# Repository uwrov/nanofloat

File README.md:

# NanoFloat

# Helpful Links:
>[Micropython Docs](https://docs.micropython.org/en/latest/esp32/quickref.html)

>[WebREPL GitHub](https://github.com/micropython/webrepl)

>[Seeed Studio ESP32C6 (Latest Version) Pinout](https://wiki.seeedstudio.com/xiao_esp32c6_getting_started/)

>[Seeed Studio ESP32C3 Pinout](https://wiki.seeedstudio.com/xiao_esp32c6_getting_started/)

>[DRV-8833 Motor Driver Pinout and User Guide](https://lastminuteengineers.com/drv8833-arduino-tutorial/)

>[Blue Robotics Pressure Sensor](https://bluerobotics.com/store/sensors-cameras/sensors/bar02-sensor-r1-rp/)

>[Flashing Micropython Firmware Reference Guide](https://docs.micropython.org/en/latest/esp32/tutorial/intro.html#esp32-intro)

>[MS583730BA01-50 Pressure Sensor Datasheet](https://www.te.com/usa-en/product-MS583730BA01-50.datasheet.pdf)

>[MS5837 Official Python Library](https://github.com/bluerobotics/ms5837-python)

>[Standalone Pressure Sensor DigiKey Page](https://www.digikey.com/en/products/detail/te-connectivity-measurement-specialties/MS583730BA01-50/5629501)

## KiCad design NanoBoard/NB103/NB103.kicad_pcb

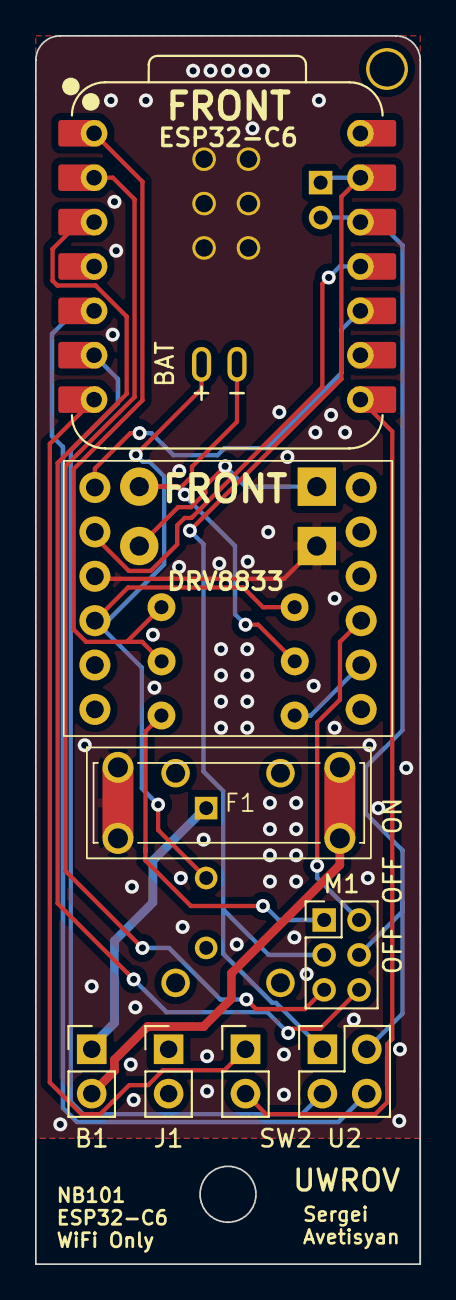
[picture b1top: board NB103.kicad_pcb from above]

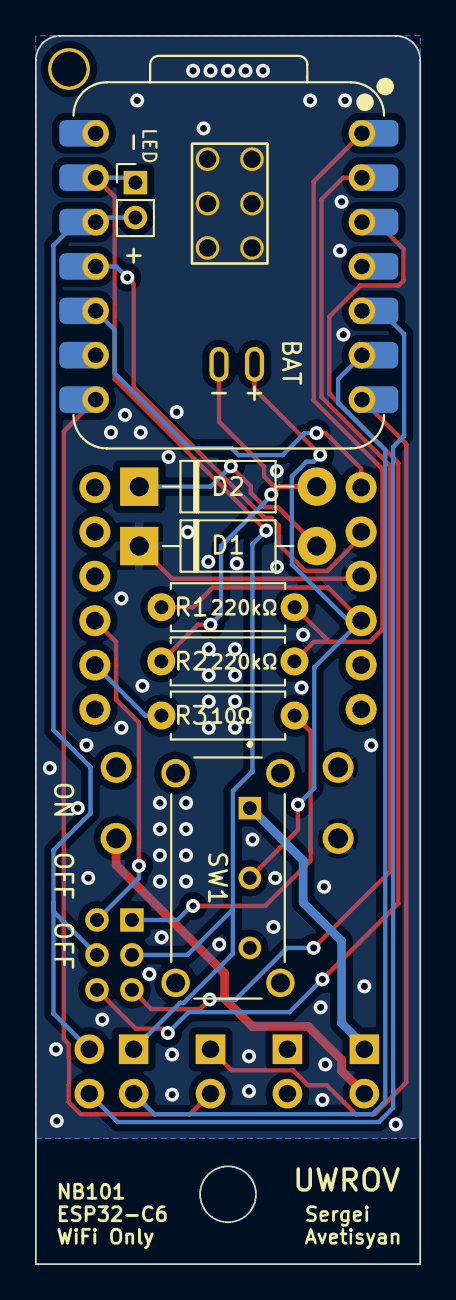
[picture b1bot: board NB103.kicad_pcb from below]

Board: 2 copper layers, 22.0 x 70.3 mm, 17 parts (8 on the bottom side), 18 nets.

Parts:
B1: 6V; PinHeader_1x02_P2.54mm_Vertical
BAT: PinHeader_1x02_P2.54mm_Vertical
D1, D2: Rectifier Diode; D_DO-41_SOD81_P10.16mm_Horizontal
F1: 0.5A Fuse; Fuse-Holder-01110501Z
J1: Motor_DC; PinHeader_1x02_P2.54mm_Vertical
LED: PinHeader_1x02_P2.00mm_Vertical
M1, M1#2: PinHeader_2x03_P2.00mm_Vertical
R1, R2: 220kOhm; R_Axial_DIN0207_L6.3mm_D2.5mm_P7.62mm_Horizontal
R3: 10 Ohm; R_Axial_DIN0207_L6.3mm_D2.5mm_P7.62mm_Horizontal
SW1: SW; Slide-Switch-EG1224
SW2: Limit Switch; PinHeader_1x02_P2.54mm_Vertical
U1: XiaoESP32C6; XIAO-ESP32C6-DIP
U2: MS583730BA01-50; PinHeader_2x02_P2.54mm_Vertical
U3: DRV8833-THT

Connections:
unnamed: B1.1 (+), SW1.1 (A)
unnamed: B1.2 (-), F1.2
unnamed: D1.2 (A), D2.1 (K)
unnamed: D1.1 (K), F1.1, U3.10 (GND)
unnamed: BAT.2, D2.2 (A), R2.1
unnamed: M1#2.2, U3.4 (Out3)
unnamed: M1#2.1, R3.2
unnamed: BAT.1, R1.1, SW1.2 (B), U3.9 (VCC)
unnamed: SW2.1 (COM), U1.7 (D6)
unnamed: SW2.2 (NC), U1.8 (D7)
unnamed: R1.2, R2.2, U1.1 (D0)
unnamed: U1.5 (D4_SDA), U2.4 (SDA)
unnamed: U1.6 (D5_SCL), U2.3 (SCL)
unnamed: U1.10 (D9), U3.12 (In4)
unnamed: U1.11 (D10), U3.11 (In3)
unnamed: LED.1, M1#2.3, U1.13 (GND), U2.1 (GND)
unnamed: LED.2, M1#2.4, U1.12 (VCC_3V3), U2.2 (VDD)
unnamed: R3.1, U3.5 (Out4)

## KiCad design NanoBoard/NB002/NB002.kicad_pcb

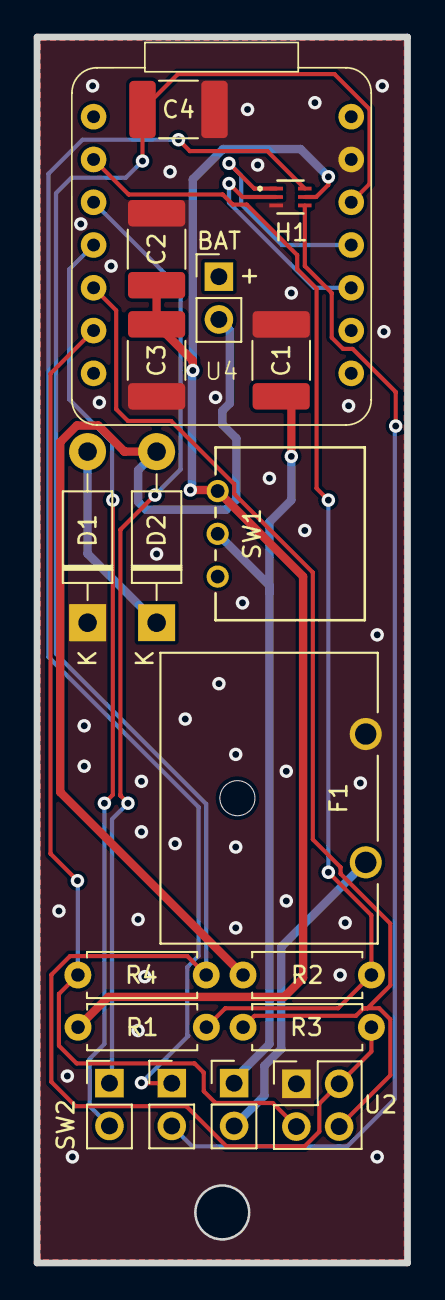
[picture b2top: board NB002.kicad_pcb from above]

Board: 2 copper layers, 22.0 x 72.8 mm, 19 parts (0 on the bottom side), 13 nets.

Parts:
B4: 1.5V; PinHeader_1x02_P2.54mm_Vertical
BAT: PinHeader_1x02_P2.54mm_Vertical
C1, C2, C3, C4: C_Small; C_1812_4532Metric_Pad1.57x3.40mm_HandSolder
D1, D2: Rectifier Diode; D_DO-41_SOD81_P10.16mm_Horizontal
F1: 2A Fuse; FUSE_01530007Z
H1: DRV8220DRLR
M1: Motor_DC; PinHeader_1x02_P2.54mm_Vertical
R1, R2: 220kOhm; R_Axial_DIN0207_L6.3mm_D2.5mm_P7.62mm_Horizontal
R3, R4: 10kOhm; R_Axial_DIN0207_L6.3mm_D2.5mm_P7.62mm_Horizontal
SW1: SW; SW_09.10290.01_EAO
SW2: Limit Switch; PinHeader_1x02_P2.54mm_Vertical
U2: MS583730BA01-50; PinHeader_2x02_P2.54mm_Vertical
U4: XiaoESP32C3; XIAO_ESP32C3_THT

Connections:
unnamed: B4.1 (+), C1.1, SW1.1 (A)
unnamed: B4.2 (-), F1.2
unnamed: D1.2 (A), D2.1 (K)
unnamed: C1.2, C2.2, C3.1, C4.2, D1.1 (K), F1.1, H1.3, U2.1 (GND), U4.GND
unnamed: BAT.2, D2.2 (A), R2.1
unnamed: H1.1, U4.10 (D9)
unnamed: H1.6, M1.1 (+)
unnamed: H1.4, M1.2 (-)
unnamed: C2.1, C3.2, H1.5, R1.1, SW1.2 (B)
unnamed: R4.1, U2.3 (SCL), U4.5 (D4_SDA)
unnamed: R3.2, U2.4 (SDA), U4.4 (D3)
unnamed: C4.1, R3.1, R4.2, U2.2 (VDD), U4.3V3
unnamed: R1.2, R2.2, U4.1 (D0)

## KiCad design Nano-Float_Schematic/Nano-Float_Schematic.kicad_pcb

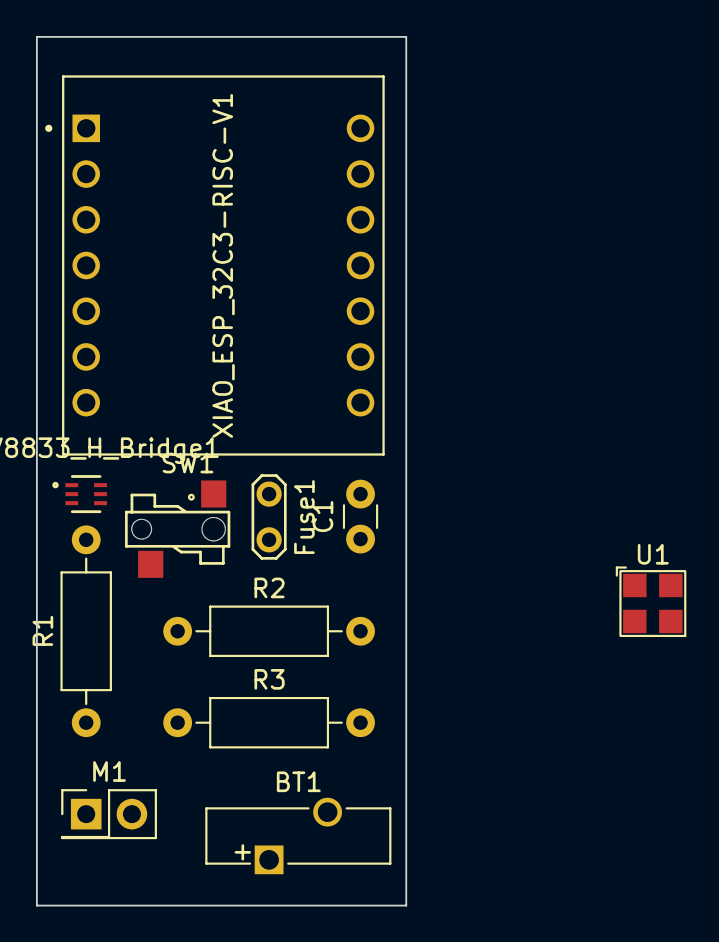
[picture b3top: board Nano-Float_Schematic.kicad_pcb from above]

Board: 2 copper layers, 20.5 x 48.3 mm, 11 parts (0 on the bottom side), 6 nets, no tracks yet.

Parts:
BT1: Battery; Battery_Panasonic_CR1025-VSK_Vertical_CircularHoles
C1: C_Small; C_Disc_D3.0mm_W1.6mm_P2.50mm
DRV8833_H_Bridge1: SOT5X3-6_DRL_TEX
Fuse1: Fuse; TestPoint_2Pads_Pitch2.54mm_Drill0.8mm
M1: Motor_DC; PinHeader_2x01_P2.54mm_Vertical
R1: R_US; R_Axial_DIN0207_L6.3mm_D2.5mm_P10.16mm_Horizontal
R2, R3: R; R_Axial_DIN0207_L6.3mm_D2.5mm_P10.16mm_Horizontal
SW1: SW_DIP_x01; SW_ESE-22MV21T
U1: MS5837-xxBA; TE_MS5837-xxBA
XIAO_ESP_32C3-RISC-V1: MODULE_102010388

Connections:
3V3: C1.2, R1.1, R2.2, R3.2, U1.2 (VDD)
D10: R1.2, SW1.2
GND: C1.1, Fuse1.2, SW1.1, U1.1 (GND)
unnamed: BT1.2 (-), Fuse1.1
unnamed: R2.1, U1.3 (SCL)
SDA: R3.1, U1.4 (SDA)

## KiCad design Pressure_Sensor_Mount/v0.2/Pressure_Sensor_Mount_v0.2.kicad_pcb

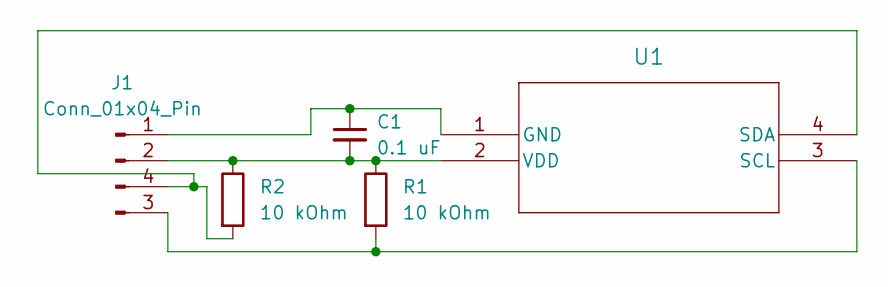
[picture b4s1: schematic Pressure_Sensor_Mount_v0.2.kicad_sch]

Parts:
C1: 0.1 uF; C_Disc_D3.0mm_W1.6mm_P2.50mm
J1: Conn_01x04_Pin; PinHeader_1x04_P2.54mm_Vertical
R1, R2: 10 kOhm; R_Axial_DIN0309_L9.0mm_D3.2mm_P12.70mm_Horizontal
U1: Pressure Sensor Footprint

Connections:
unnamed: C1.1, J1.1, U1.1 (GND)
unnamed: C1.2, J1.2, R1.1, R2.1, U1.2 (VDD)
unnamed: J1.3, R1.2, U1.3 (SCL)
unnamed: J1.4, R2.2, U1.4 (SDA)

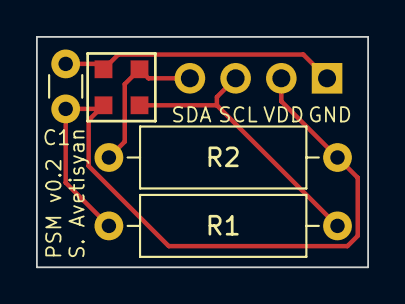
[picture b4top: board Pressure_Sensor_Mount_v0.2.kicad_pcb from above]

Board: 2 copper layers, 18.4 x 12.8 mm, 5 parts (1 on the bottom side), 4 nets.

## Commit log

2024-03-08 Prototype Pressure Sensor Mounting PCB
2024-03-08 uploading NanOS v0.0.1
    v0.0.1, as demonstrated on 3/3/2024. The first functional prototype of NanOS.
2024-03-08 Create test
2024-03-08 uploaded NanOS v0.0.1
    NanOS v0.0.1 as demonstrated on 3/3/24. The first functional prototype, many features missing but main structure is defined.
2024-03-11 Updating KiCAD project files
2024-03-11 Updated gitignore for KiCAD PCBs
2024-03-11 Added Silkscreen Text to PCB
2024-03-11 Fixed Silkscreen Error
2024-03-11 Manufacturing Changes
2024-03-11 Updated Manufacturing Plots
2024-03-12 Zipped Gerber Files for Manufacturing
2024-03-12 Updated Dive Parameters in boot.py
2024-03-12 Added Helpful Links to README.md
2024-03-12 Cleaning Up v0.0.2
2024-03-12 Cleaning boot.py v0.0.2
2024-03-13 Uploaded WLAN Config File for v0.0.2
2024-03-13 Updating Wireless Settings for v0.0.2
2024-03-13 Improving Wireless Configuration for v0.0.2
2024-03-26 Updated boot.py
2024-03-28 Uploaded pressure sensor official i2c library
2024-03-28 Updating boot.py with i2c library
2024-03-31 config check
2024-03-31 undid change
2024-03-31 Initial Full Float Schematic
2024-03-31 Update a label and add lock files to gitignore
2024-03-31 Add deep sleep
2024-03-31 deep sleep with space (format cleaner
2024-03-31 Update boot.py
    softI2C
2024-03-31 Updated Battery Circuit to implement the fuse correctly and added to-do list
2024-04-02 Updated with global labels
2024-04-05 work on dive function
2024-04-05 dive function work
2024-04-07 Add *.DS_Store to .gitignore
2024-04-11 Modified boot.py and KiCad Schematic
2024-04-12 Uploaded new pressure sensor mount schematic and PCB
2024-04-13 Updated PSM v0.2
2024-04-14 Got the Footprints! Need to play around more with the orientation of everything on the final PCB
2024-04-14 Add files via upload
    This is a temp file for the future float and uwrov user interaction method.
2024-04-18 updated float schematic
2024-05-12 footprints? yes!
2024-05-16 Update boot.py (Add a combo of float motion)
2024-05-16 Update boot.py add break
2024-05-16 Update boot.py delete break
2024-05-26 SID -> PCB
2024-06-02 my float pcb work
2024-06-02 moving stuff around
    just making folders and such
2024-06-02 Float PCB Updates
2024-06-02 renamed folder
2024-06-10 Added Preliminary Traces for PCB
2024-06-11 Updated PCB
2024-06-11 Updated PCB and added Manufacturing Files
2024-06-11 Restructuring the Directories and Naming Conventions
2024-06-11 NB002 with Ground Plane and Mounting Edits
2024-06-12 Updated Ground Planes
2024-06-12 Added NGP PCB
2025-01-21 Full Rework of NanoBoard Libraries, Updated Final Version of NB101
2025-01-21 Testing Updates to README
2025-01-21 Added Image
2025-05-28 Updates to boards and Flashing Micropython
2025-06-14 Introduced NanOS v0.0.3 with Encoder Support
